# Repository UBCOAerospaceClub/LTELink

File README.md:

# LTELink

> [!IMPORTANT]
> This project is a work in progress

LTELink is custom base board design for the [Radxa CM3](https://radxa.com/products/cm/cm3/). It main purpose is to connect several IP cameras and other ethernet-connected devices on a drone, and stream their video and telemetry over LTE to a ground station. Additionally, a compatible WiFi adapter could be connected via USB to use [WFB-ng](https://github.com/svpcom/wfb-ng) for a direct radio link. Video streamed through the LTELink could also be recorded directly to the onboard SD card for a post-flight review.

## Hardware Specs

* 1x MiniPCIE slot for LTE modem (Designed for Quectel EC25)
* 1x Nano SIM card slot
* 1x USB 2.0 hosts
* 1x USB OTG interface with manual host/device control
* 4x 100M ethernet (unmanaged)
* 1x Micro SD card slot
* 2x UART connectors

## Hardware Block Diagram

## Software Stack

* GStreamer for video streaming
* mavp2p for Mavlink routing
* Tailscale for VPN
* Rockchip Media Processing Pipeline for video encoding (if needed)

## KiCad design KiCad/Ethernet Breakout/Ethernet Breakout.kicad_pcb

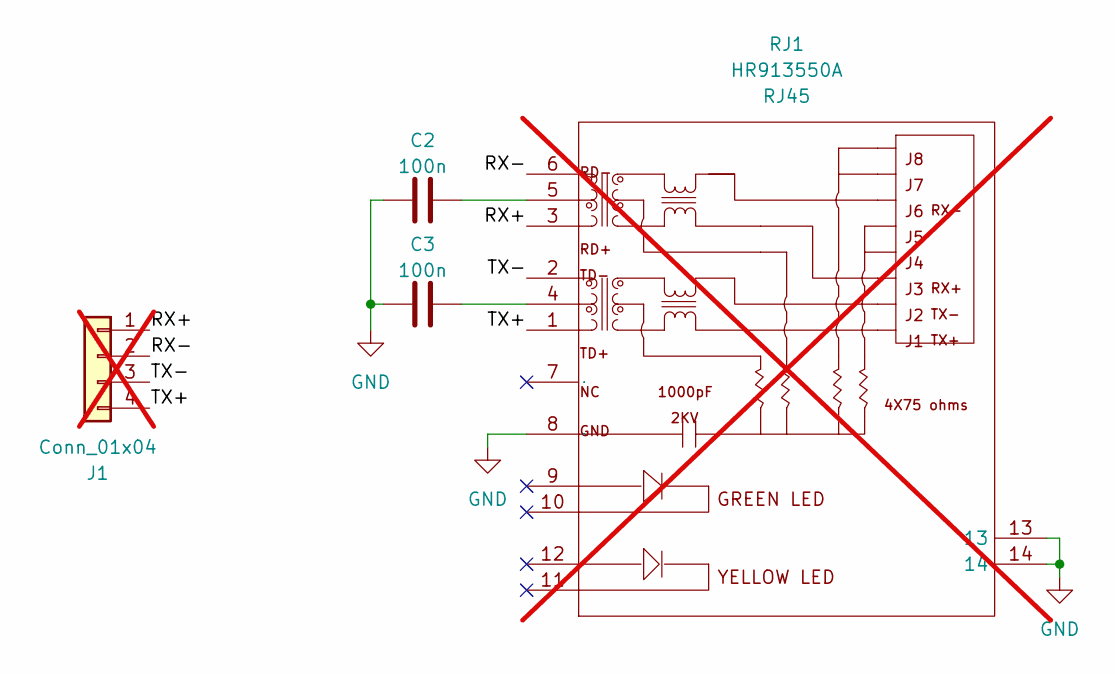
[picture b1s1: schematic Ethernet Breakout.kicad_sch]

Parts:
C2, C3: 100n; C_0603_1608Metric_Pad1.08x0.95mm_HandSolder; LCSC Part # C1525
J1: Conn_01x04; PinHeader_1x04_P2.54mm_Vertical; not fitted
RJ1: HR913550A; not fitted

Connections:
/RX+: J1.1, RJ1.3
/RX-: J1.2, RJ1.6
/TX+: J1.4, RJ1.1
/TX-: J1.3, RJ1.2
GND: C2.1, C3.1, RJ1.8 (GND), RJ1.13, RJ1.14
unnamed: C2.2, RJ1.5
unnamed: C3.2, RJ1.4

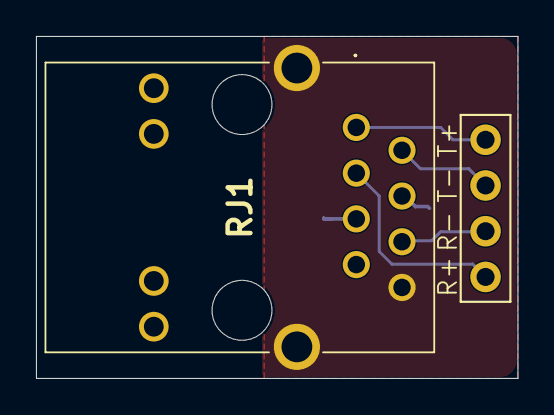
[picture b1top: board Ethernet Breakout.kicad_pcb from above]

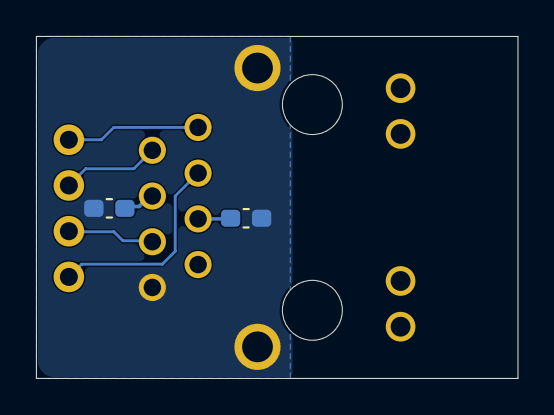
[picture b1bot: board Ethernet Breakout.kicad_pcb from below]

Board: 2 copper layers, 26.8 x 19.0 mm, 4 parts (2 on the bottom side), 7 nets.

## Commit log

2025-11-25 Add CERN Open Hardware Licence Version 2
    Added CERN Open Hardware Licence Version 2 - Weakly Reciprocal to the project.
2025-11-25 Expand README with project details and specifications
    Expanded the README to include hardware specs, block diagram, and software stack details.
2025-11-25 Fix typo in ethernet description in README.md
2025-11-30 Enhance README with project details and links
    Added links to Radxa CM3 and WFB-ng, and included information about video recording to SD card.
2026-01-07 update current state of project
2026-01-22 mostly done except for RTL8305 power stuff
2026-01-24 most traces complete. need to connect grounds
2026-01-25 Wiring complete!
2026-01-29 Finally done the layout
2026-02-04 Finalized layout, added more detailed 3d models
2026-02-06 replaced ferrites with 0 omh resitors, finalized standoff solution
2026-02-06 fix ethernet skews
2026-02-07 finalized board for fabrication
2026-02-11 fix incorrect footprint orientation and breakout uarts
2026-03-29 fixed CM3 footprint
2026-04-02 Progress on V2.0 and file structure reformat
2026-04-02 Add Ethernet Brekaout board
2026-04-02 Add USB Breakout board
2026-04-12 Moved LEDs to other side of the board, which means they mustbe assembled by hand. Added UART 5 test points.
2026-06-09 Finalized Ethernet Breakout for production
2026-06-09 Finalized USB Breakout for production
2026-06-09 Finalize LTELink V2 for production
2026-06-09 remove old backups
